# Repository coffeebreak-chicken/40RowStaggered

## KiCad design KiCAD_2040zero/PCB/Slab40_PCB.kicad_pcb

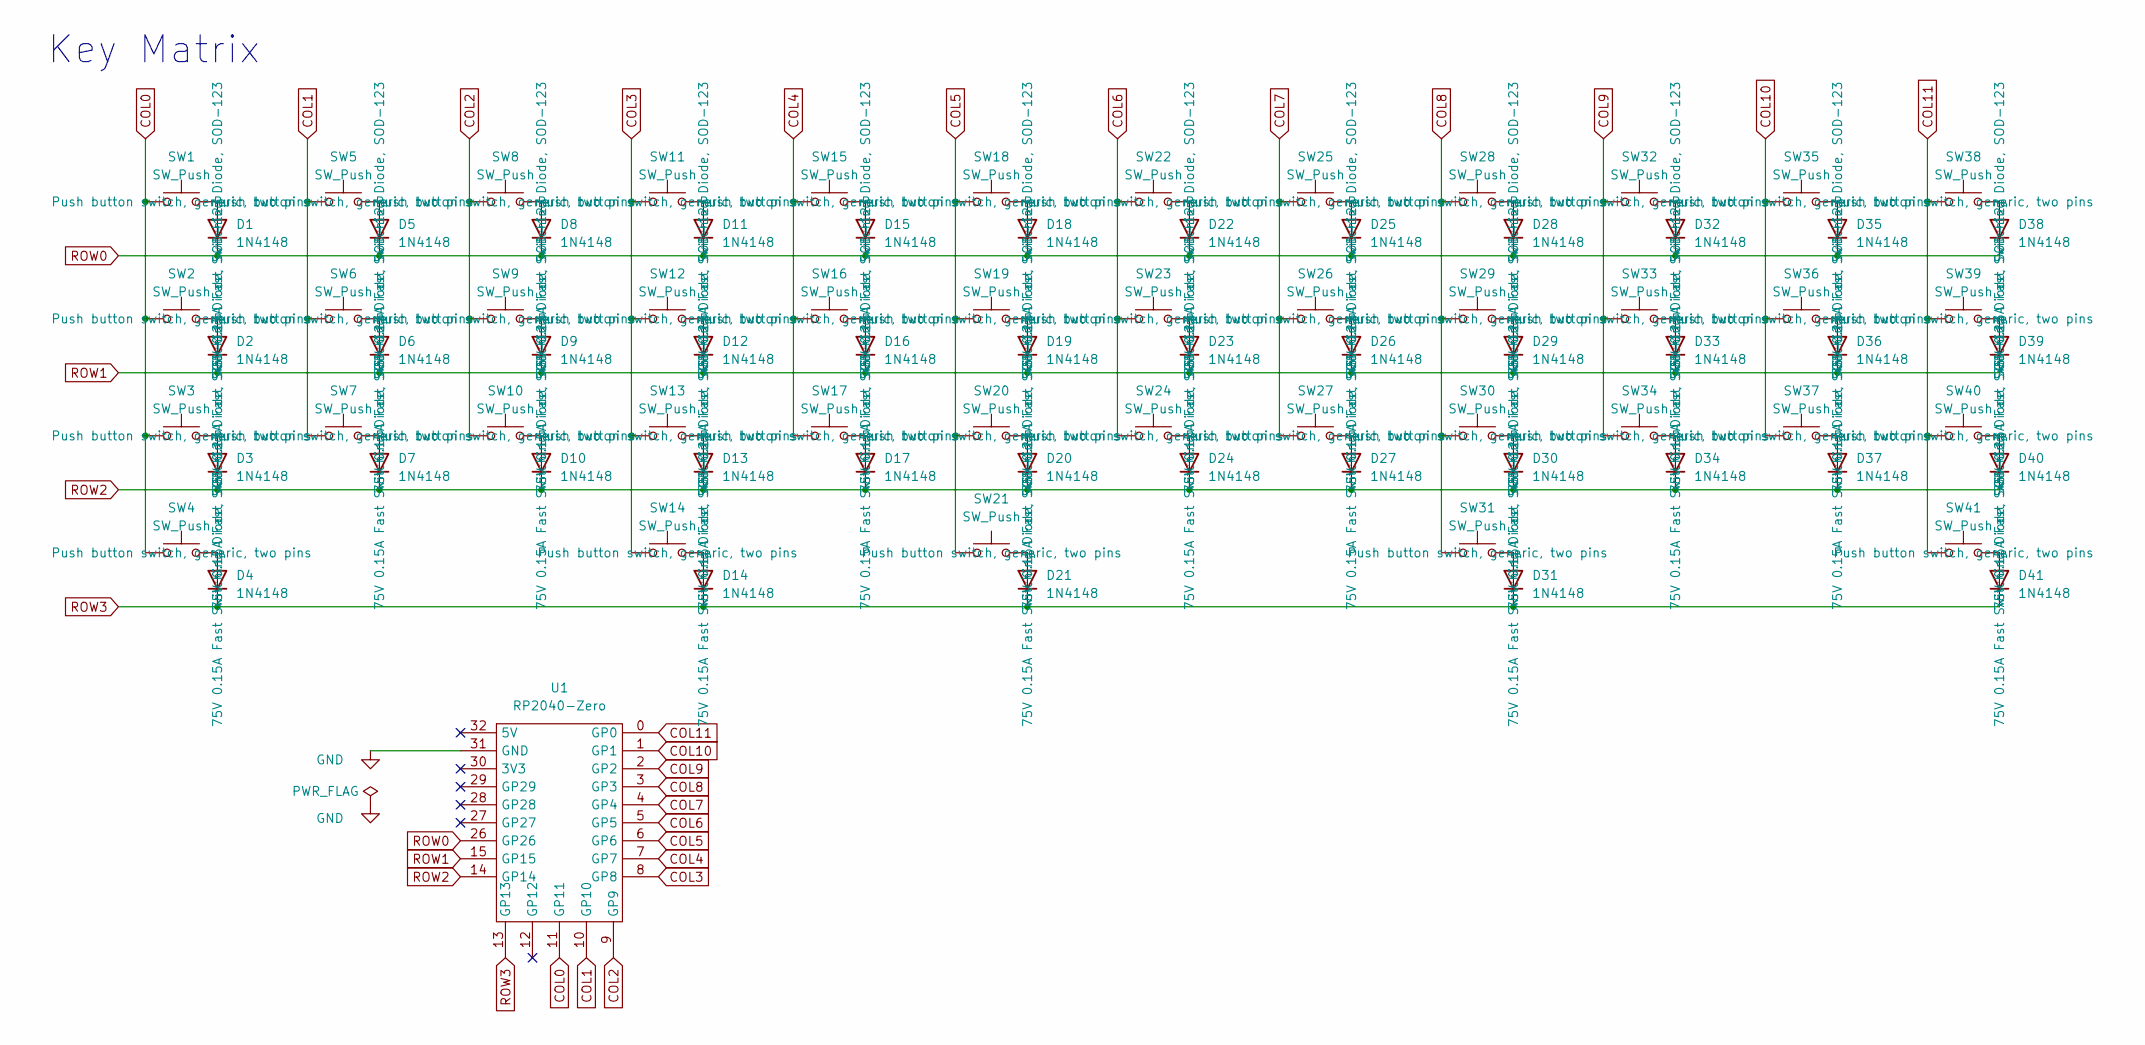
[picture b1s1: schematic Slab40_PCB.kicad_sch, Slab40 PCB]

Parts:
D1, D2, D3, D4, D5, D6, D7, D8, D9, D10, D11, D12, D13, D14, D15, D16, D17, D18, D19, D20, D21, D22, D23, D24, D25, D26, D27, D28, D29, D30, D31, D32, D33, D34, D35, D36, D37, D38, D39, D40, D41: 1N4148; D_DO-35_SOD27_P7.62mm_Horizontal; LCSC Parts # C81598
SW1, SW40: SW_Push; MX_Socket_1.25U
SW2, SW4, SW39, SW41: SW_Push; MX_Socket_1.50U
SW3, SW38: SW_Push; MX_Socket_1.75U
SW5, SW6, SW7, SW8, SW9, SW10, SW11, SW12, SW13, SW14, SW15, SW16, SW17, SW18, SW19, SW20, SW21, SW22, SW23, SW24, SW25, SW26, SW27, SW28, SW29, SW30, SW31, SW32, SW33, SW34, SW35, SW36, SW37: SW_Push; MX_Socket
U1: RP2040-Zero; RP2040-Zero-THT

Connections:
COL0: SW1.1, SW2.1, SW3.1, SW4.1, U1.11 (GP11)
COL1: SW5.1, SW6.1, SW7.1, U1.10 (GP10)
COL2: SW8.1, SW9.1, SW10.1, U1.9 (GP9)
COL3: SW11.1, SW12.1, SW13.1, SW14.1, U1.8 (GP8)
COL4: SW15.1, SW16.1, SW17.1, U1.7 (GP7)
COL5: SW18.1, SW19.1, SW20.1, SW21.1, U1.6 (GP6)
COL6: SW22.1, SW23.1, SW24.1, U1.5 (GP5)
COL7: SW25.1, SW26.1, SW27.1, U1.4 (GP4)
COL8: SW28.1, SW29.1, SW30.1, SW31.1, U1.3 (GP3)
COL9: SW32.1, SW33.1, SW34.1, U1.2 (GP2)
COL10: SW35.1, SW36.1, SW37.1, U1.1 (GP1)
COL11: SW38.1, SW39.1, SW40.1, SW41.1, U1.0 (GP0)
GND: U1.31 (GND)
unnamed: D1.2 (A), SW1.2
unnamed: D2.2 (A), SW2.2
unnamed: D3.2 (A), SW3.2
unnamed: D4.2 (A), SW4.2
unnamed: D5.2 (A), SW5.2
unnamed: D6.2 (A), SW6.2
unnamed: D7.2 (A), SW7.2
unnamed: D8.2 (A), SW8.2
unnamed: D9.2 (A), SW9.2
unnamed: D10.2 (A), SW10.2
unnamed: D11.2 (A), SW11.2
unnamed: D12.2 (A), SW12.2
unnamed: D13.2 (A), SW13.2
unnamed: D14.2 (A), SW14.2
unnamed: D15.2 (A), SW15.2
unnamed: D16.2 (A), SW16.2
unnamed: D17.2 (A), SW17.2
unnamed: D18.2 (A), SW18.2
unnamed: D19.2 (A), SW19.2
unnamed: D20.2 (A), SW20.2
unnamed: D21.2 (A), SW21.2
unnamed: D22.2 (A), SW22.2
unnamed: D23.2 (A), SW23.2
unnamed: D24.2 (A), SW24.2
unnamed: D25.2 (A), SW25.2
unnamed: D26.2 (A), SW26.2
unnamed: D27.2 (A), SW27.2
unnamed: D28.2 (A), SW28.2
unnamed: D29.2 (A), SW29.2
unnamed: D30.2 (A), SW30.2
unnamed: D31.2 (A), SW31.2
unnamed: D32.2 (A), SW32.2
unnamed: D33.2 (A), SW33.2
unnamed: D34.2 (A), SW34.2
unnamed: D35.2 (A), SW35.2
unnamed: D36.2 (A), SW36.2
unnamed: D37.2 (A), SW37.2
unnamed: D38.2 (A), SW38.2
unnamed: D39.2 (A), SW39.2
unnamed: D40.2 (A), SW40.2
unnamed: D41.2 (A), SW41.2
ROW0: D1.1 (K), D5.1 (K), D8.1 (K), D11.1 (K), D15.1 (K), D18.1 (K), D22.1 (K), D25.1 (K), D28.1 (K), D32.1 (K), D35.1 (K), D38.1 (K), U1.26 (GP26)
ROW1: D2.1 (K), D6.1 (K), D9.1 (K), D12.1 (K), D16.1 (K), D19.1 (K), D23.1 (K), D26.1 (K), D29.1 (K), D33.1 (K), D36.1 (K), D39.1 (K), U1.15 (GP15)
ROW2: D3.1 (K), D7.1 (K), D10.1 (K), D13.1 (K), D17.1 (K), D20.1 (K), D24.1 (K), D27.1 (K), D30.1 (K), D34.1 (K), D37.1 (K), D40.1 (K), U1.14 (GP14)
ROW3: D4.1 (K), D14.1 (K), D21.1 (K), D31.1 (K), D41.1 (K), U1.13 (GP13)

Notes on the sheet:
Key Matrix

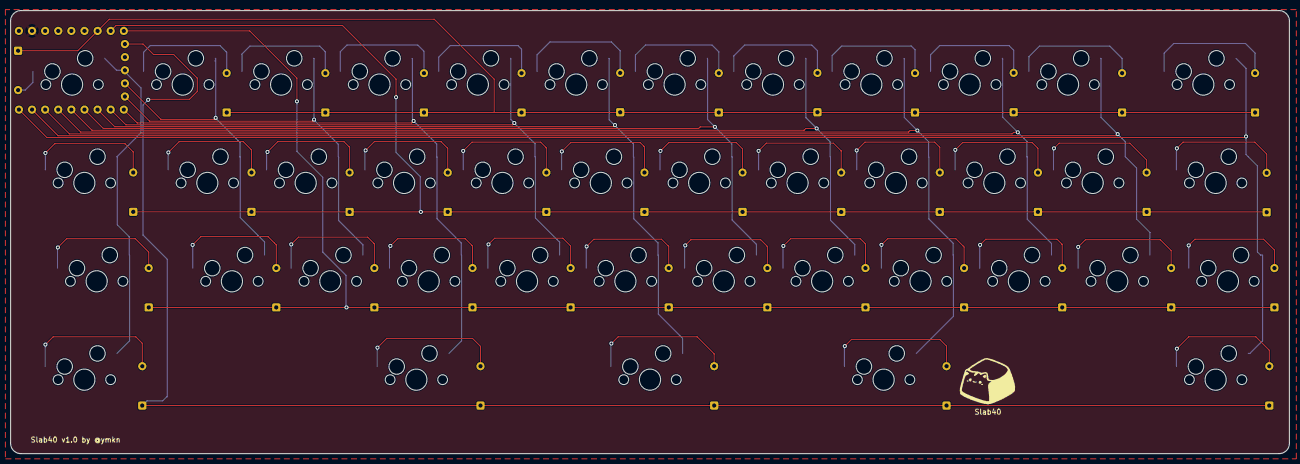
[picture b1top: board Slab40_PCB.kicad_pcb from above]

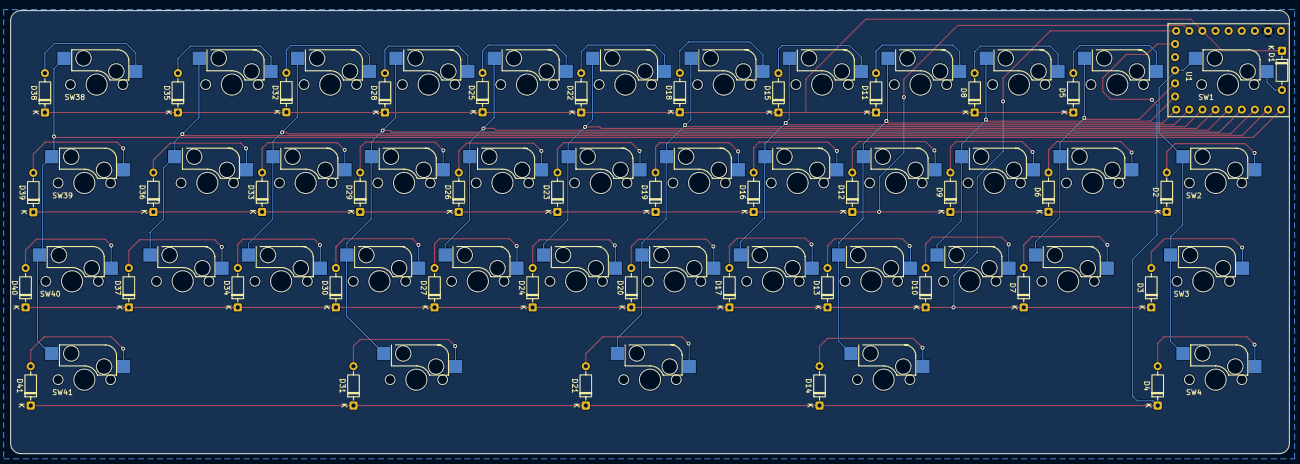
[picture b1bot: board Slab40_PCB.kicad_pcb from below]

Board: 2 copper layers, 247.6 x 85.8 mm, 83 parts (83 on the bottom side), 57 nets.

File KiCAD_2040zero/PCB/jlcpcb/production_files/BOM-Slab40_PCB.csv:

Comment,Designator,Footprint,LCSC,Quantity
1N4148,"D1,D10,D11,D12,D13,D14,D15,D16,D17,D18,D19,D2,D20,D21,D22,D23,D24,D25,D26,D27,D28,D29,D3,D30,D31,D32,D33,D34,D35,D36,D37,D38,D39,D4,D40,D41,D5,D6,D7,D8,D9",D_DO-35_SOD27_P7.62mm_Horizontal,C81598,41
SW_Push,SW20,MX_Socket,,1
SW_Push,SW31,MX_Socket,,1
SW_Push,SW5,MX_Socket,,1
SW_Push,SW41,MX_Socket_1.50U,,1
SW_Push,SW8,MX_Socket,,1
SW_Push,SW33,MX_Socket,,1
SW_Push,SW34,MX_Socket,,1
SW_Push,SW30,MX_Socket,,1
SW_Push,SW37,MX_Socket,,1
SW_Push,SW14,MX_Socket,,1
SW_Push,SW39,MX_Socket_1.50U,,1
SW_Push,SW38,MX_Socket_1.75U,,1
SW_Push,SW9,MX_Socket,,1
SW_Push,SW40,MX_Socket_1.25U,,1
SW_Push,SW12,MX_Socket,,1
SW_Push,SW23,MX_Socket,,1
SW_Push,SW16,MX_Socket,,1
SW_Push,SW28,MX_Socket,,1
SW_Push,SW27,MX_Socket,,1
SW_Push,SW10,MX_Socket,,1
SW_Push,SW25,MX_Socket,,1
SW_Push,SW17,MX_Socket,,1
SW_Push,SW1,MX_Socket_1.25U,,1
SW_Push,SW13,MX_Socket,,1
SW_Push,SW15,MX_Socket,,1
SW_Push,SW35,MX_Socket,,1
SW_Push,SW32,MX_Socket,,1
SW_Push,SW22,MX_Socket,,1
SW_Push,SW36,MX_Socket,,1
SW_Push,SW11,MX_Socket,,1
SW_Push,SW19,MX_Socket,,1
RP2040-Zero,U1,RP2040-Zero-THT,,1
SW_Push,SW29,MX_Socket,,1
SW_Push,SW2,MX_Socket_1.50U,,1
SW_Push,SW21,MX_Socket,,1
SW_Push,SW7,MX_Socket,,1
SW_Push,SW18,MX_Socket,,1
SW_Push,SW6,MX_Socket,,1
SW_Push,SW26,MX_Socket,,1
SW_Push,SW4,MX_Socket_1.50U,,1
SW_Push,SW24,MX_Socket,,1
SW_Push,SW3,MX_Socket_1.75U,,1

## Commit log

2025-09-21 ymkn氏Slab40オリジナル
2025-09-21 PCBデータ
2025-09-21 rp2040ファームウェア
